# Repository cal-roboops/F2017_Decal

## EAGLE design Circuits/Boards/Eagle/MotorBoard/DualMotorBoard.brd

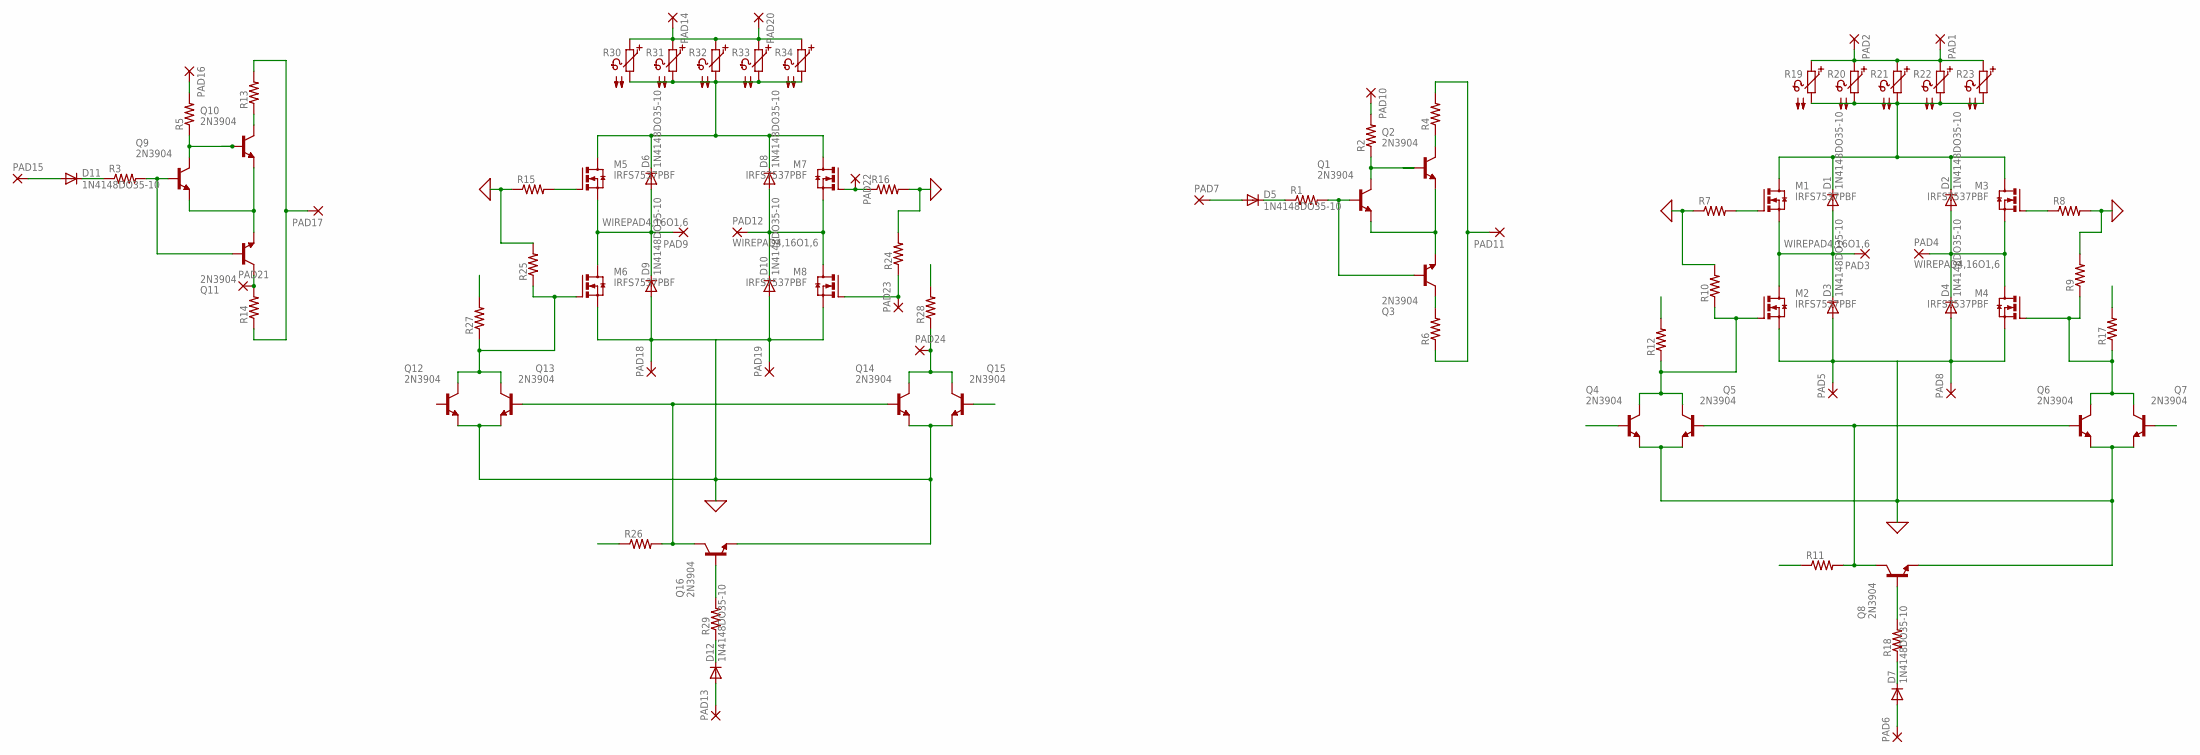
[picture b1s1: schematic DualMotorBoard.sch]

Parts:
D1, D2, D3, D4, D5, D6, D7, D8, D9, D10, D11, D12: 1N4148DO35-10; DO35-10
M1, M2, M3, M4, M5, M6, M7, M8: IRFS7537PBF; D2PACK
PAD1, PAD2, PAD5, PAD8, PAD14, PAD18, PAD19, PAD20: 3,81/1,4
PAD3, PAD4, PAD9, PAD12: WIREPAD4,16O1,6; 4,16O1,6
PAD6, PAD10, PAD11, PAD13, PAD16, PAD17, PAD21, PAD22, PAD23, PAD24: 2,54/1,1
PAD7, PAD15: 2,54/1,0
Q1, Q2, Q3, Q4, Q5, Q6, Q7, Q8, Q9, Q10, Q11, Q12, Q13, Q14, Q15, Q16: 2N3904; TO92
R1, R2, R3, R4, R5, R6, R7, R8, R9, R10, R11, R12, R13, R14, R15, R17, R18, R25, R26, R27, R28, R29: R-US_0207/7; 0207/7
R16, R24: R-US_0207/12; 0207/12
R19, R20, R21, R22, R23, R30, R31, R32, R33, R34: PTC660A; P660A

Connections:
0: D3.A, D4.A, D9.A, D10.A, M2.3 (S), M4.3 (S), M6.3 (S), M8.3 (S), PAD5.1, PAD8.1, PAD18.1, PAD19.1, Q1.3 (E), Q2.3 (E), Q3.3 (E), Q4.3 (E), Q5.3 (E), Q6.3 (E), Q7.3 (E), Q8.3 (E), Q9.3 (E), Q10.3 (E), Q11.3 (E), Q12.3 (E), Q13.3 (E), Q14.3 (E), Q15.3 (E), Q16.3 (E), R7.1, R8.2, R9.2, R10.2, R15.1, R16.2, R24.2, R25.2
BB: Q1.2 (B), Q3.2 (B), Q4.2 (B), R1.2
BB1: Q9.2 (B), Q11.2 (B), R3.2
BF: M3.1 (G), Q3.1 (C), R6.2, R8.1
BFF: PAD21.1, Q11.1 (C), R14.2
BFG: M7.1 (G), PAD22.1, R16.1
DIR: D5.A, PAD7.1
DIR1: D11.A, PAD15.1
FB: Q1.1 (C), Q2.2 (B), Q7.2 (B), R2.1
FB1: Q9.1 (C), Q10.2 (B), Q15.2 (B), R5.1
FF: M1.1 (G), Q2.1 (C), R4.1, R7.2
FF1: M5.1 (G), Q10.1 (C), R13.1, R15.2
MN: D2.A, D4.C, M3.3 (S), M4.2 (D), PAD4.1
MN1: D8.A, D10.C, M7.3 (S), M8.2 (D), PAD12.1
MP: D1.A, D3.C, M1.3 (S), M2.2 (D), PAD3.1
MP1: D6.A, D9.C, M5.3 (S), M6.2 (D), PAD9.1
unnamed: M8.1 (G), PAD23.1, R24.1
unnamed: D7.C, R18.1
unnamed: M6.1 (G), Q12.1 (C), Q13.1 (C), R25.1, R27.1
unnamed: D7.A, PAD6.1
unnamed: PAD24.1, Q14.1 (C), Q15.1 (C), R28.1
unnamed: Q13.2 (B), Q14.2 (B), Q16.1 (C), R26.2
unnamed: Q16.2 (B), R29.2
unnamed: D11.C, R3.1
unnamed: D12.C, R29.1
unnamed: D12.A, PAD13.1
unnamed: Q5.2 (B), Q6.2 (B), Q8.1 (C), R11.2
unnamed: D5.C, R1.1
unnamed: M2.1 (G), Q4.1 (C), Q5.1 (C), R10.1, R12.1
unnamed: Q8.2 (B), R18.2
unnamed: M4.1 (G), Q6.1 (C), Q7.1 (C), R9.1, R17.1
VBAT: PAD1.1, PAD2.1, PAD14.1, PAD20.1, R19.1, R20.1, R21.1, R22.1, R23.1, R30.1, R31.1, R32.1, R33.1, R34.1
VDD: D1.C, D2.C, M1.2 (D), M3.2 (D), R19.2, R20.2, R21.2, R22.2, R23.2
VDD1: D6.C, D8.C, M5.2 (D), M7.2 (D), R30.2, R31.2, R32.2, R33.2, R34.2
VG: PAD11.1, R4.2, R6.1, R12.2, R17.2
VG1: PAD17.1, R13.2, R14.1, R27.2, R28.2
VSW: PAD10.1, R2.2, R11.1
VSW1: PAD16.1, R5.2, R26.1

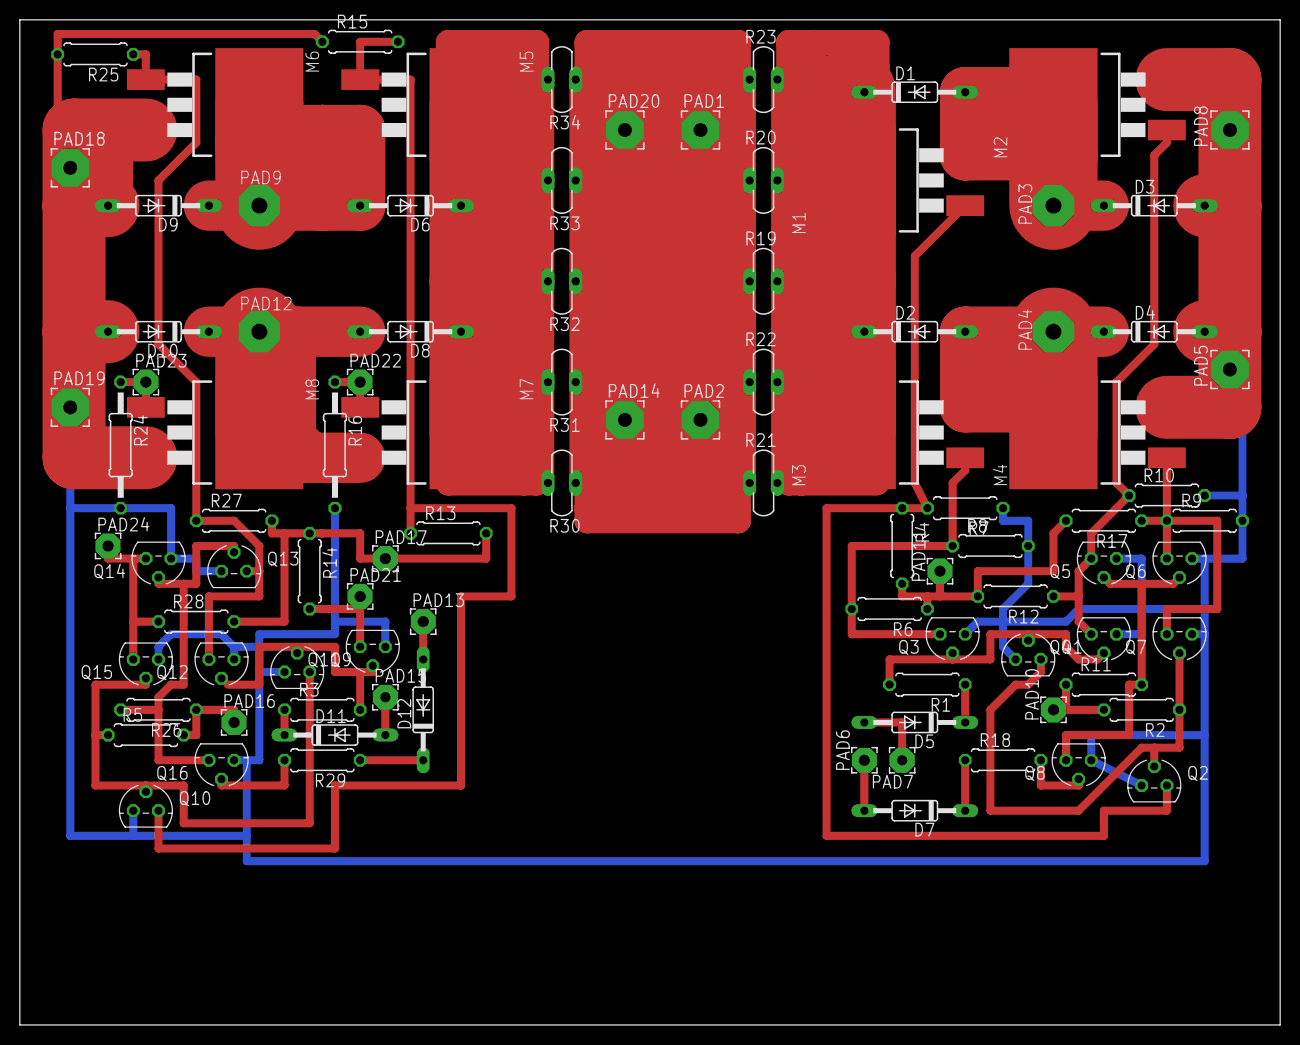
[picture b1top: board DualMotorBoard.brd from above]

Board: 2 copper layers, 127.0 x 101.3 mm, 94 parts (0 on the bottom side), 38 nets.

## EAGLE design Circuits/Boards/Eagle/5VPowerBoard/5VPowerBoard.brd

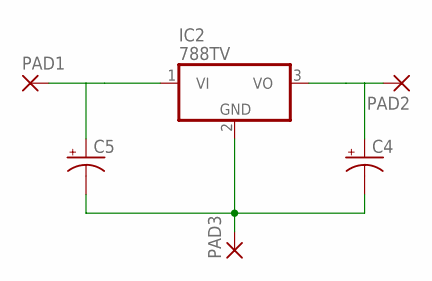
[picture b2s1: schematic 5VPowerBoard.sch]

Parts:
C4, C5: CPOL-USE2.5-7; E2,5-7
IC2: 788TV; TO220V
PAD1, PAD2, PAD3: 3,81/1,4

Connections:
unnamed: C4.-, C5.-, IC2.2 (GND), PAD3.1
VDD: C5.+, IC2.1 (VI), PAD1.1
VSW: C4.+, IC2.3 (VO), PAD2.1

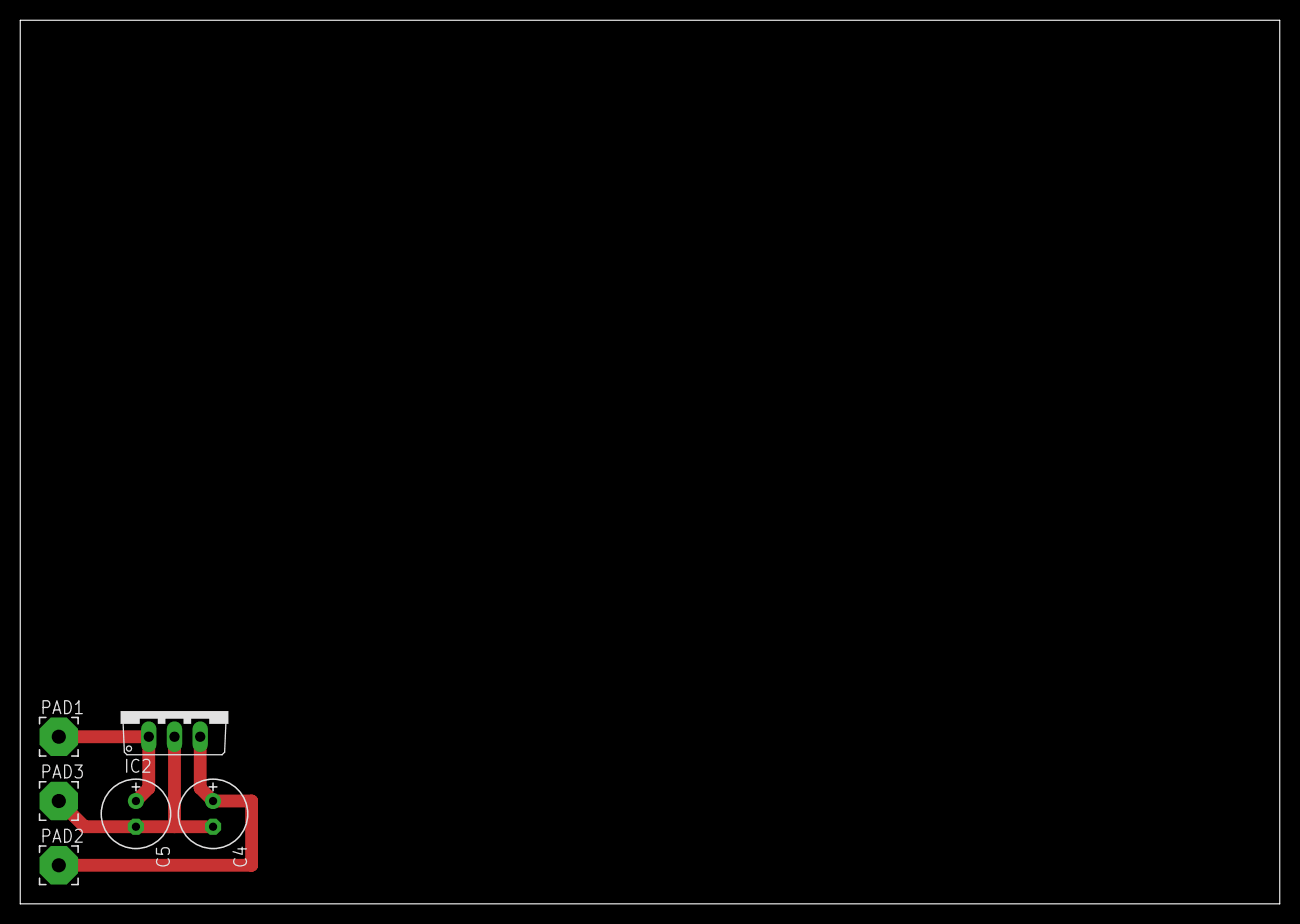
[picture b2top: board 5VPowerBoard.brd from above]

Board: 2 copper layers, 124.4 x 87.3 mm, 6 parts (0 on the bottom side), 3 nets.

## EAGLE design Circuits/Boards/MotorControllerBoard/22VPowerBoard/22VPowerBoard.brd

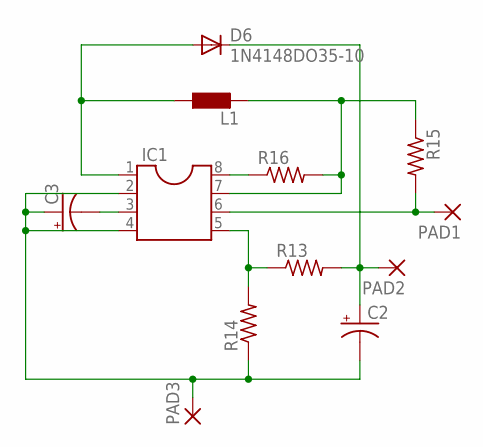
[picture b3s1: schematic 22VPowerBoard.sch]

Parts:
C2, C3: CPOL-USE2.5-7; E2,5-7
D6: 1N4148DO35-10; DO35-10
IC1: DIL8; DIL08
L1: L0207/10; 0207/10
PAD1, PAD2, PAD3: 3,81/1,4
R13, R14, R15, R16: R-US_0207/7; 0207/7

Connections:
unnamed: C2.-, C3.+, IC1.2, IC1.4, PAD3.1, R14.1
unnamed: D6.A, IC1.1, L1.1
unnamed: C3.-, IC1.3
unnamed: IC1.8, R16.1
unnamed: IC1.7, L1.2, R15.1, R16.2
unnamed: IC1.5, R13.1, R14.2
VDD: IC1.6, PAD1.1, R15.2
VG2: C2.+, D6.C, PAD2.1, R13.2

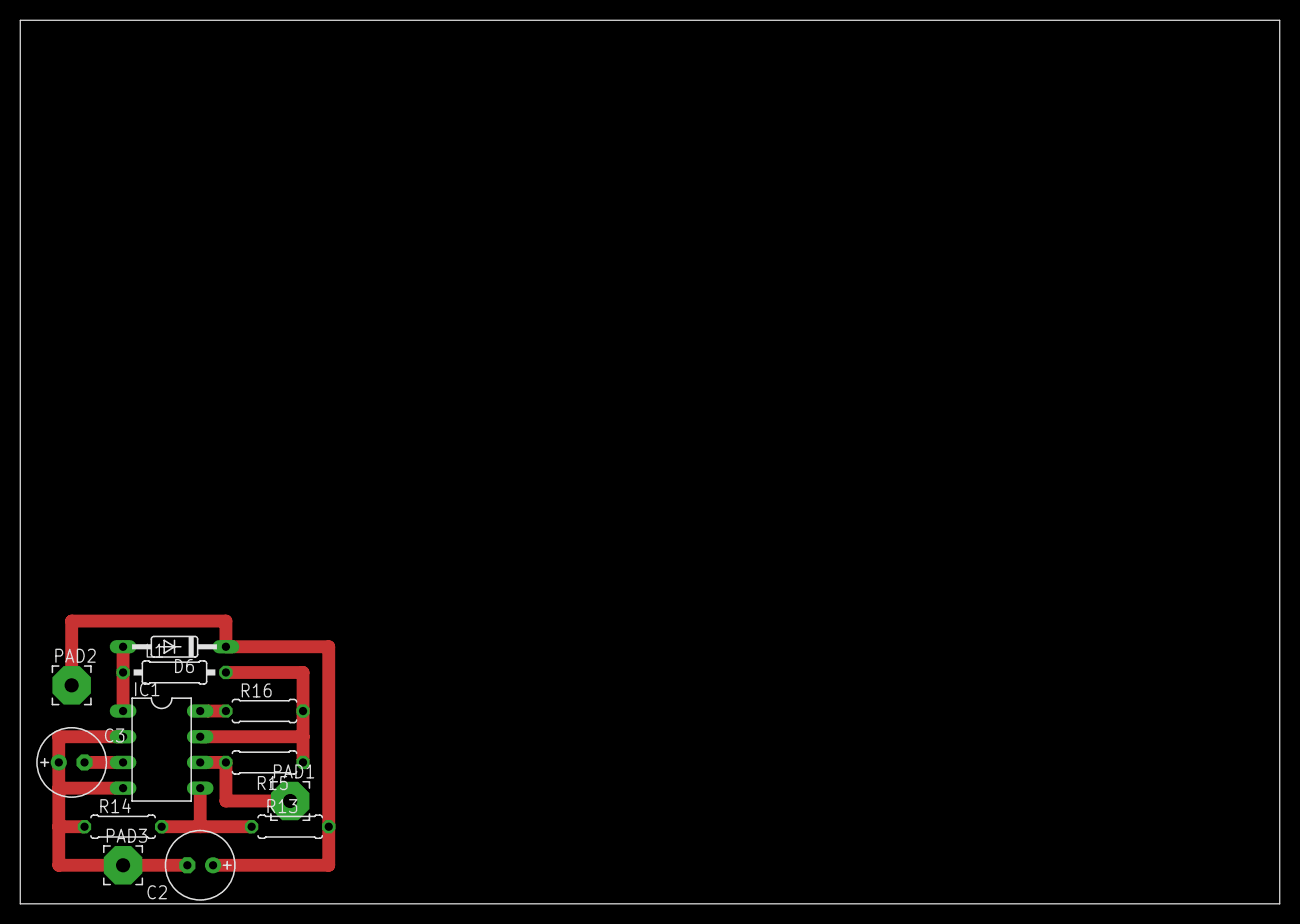
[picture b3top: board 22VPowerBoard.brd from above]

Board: 2 copper layers, 124.4 x 87.3 mm, 12 parts (0 on the bottom side), 8 nets.

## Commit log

2017-08-22 Project creation and gitignore added
2017-08-23 added button that prints to debud
2017-08-23 added text box + submit data button for text box
2017-08-24 made client server with text boxes
2017-08-24 Organization and fine tuning of messenger demo
2017-08-28 local webcam button working
2017-09-18 Added backend server, with basic client, and GUI test client
2017-09-18 Updated gitignore and removed qt exe's
2017-09-21 Added Circuit sims
2017-09-21 Making motor controller feedback loop
2017-09-21 Updated Op-Amp in Logic:
2017-09-25 Updated motor simulation
2017-09-25 Ignore simulation raw files
2017-09-26 Save point before PNP control implementation
2017-09-26 Working motor controller simulation
2017-09-27 Small changes
2017-09-27 Pathing Upload
2017-09-28 Split up motor simulation and defiend high pwoer line
2017-09-30 Updated client/server and made changes to motor controller
2017-10-01 server.cpp V4
2017-10-05 Motor controller updates
2017-10-05 Updated motor controller
2017-10-08 Updated server script and vlc multicast
2017-10-08 Updated proxy client and server classes
2017-10-08 ass1
2017-10-08 Setting up rover client
2017-10-15 deleted Circuits, Pathing, and QtMessengerDemo folders
2017-10-15 Simplified motor controller circuit and added FPGA implmentation specifications
2017-10-16 Updated regulator circuits
2017-10-17 json communication/mutexes/function structs
2017-10-17 server now communicates to rover and back to clients
2017-10-18 updated files
2017-10-18 Added custom motor controller tester
2017-10-25 update all clients
2017-10-25 miscellaneous change
2017-10-25 adding assignment3 code - edward
2017-10-25 git example change
2017-10-25 basic impl of topological pathing done
2017-10-26 cleaned up topological pathing code
2017-10-27 changed path drawing
2017-10-27 made window with buttons that change pages
2017-10-27 added regular controls panel
2017-11-01 Fixed motor controller test code - works as expected now
2017-11-01 tank page
2017-11-01 tank done -- can't move to qtproxy yet
2017-11-03 move control_GUI code to QtProxyClient and two ui windows working
2017-11-03 tank done
2017-11-04 Motor control code updated
2017-11-04 Updated gitigore and removed build-Qt dirs
2017-11-06 Updated encoder reading and motor controller
2017-11-08 updated server/client files; added json.hpp
2017-11-08 removed unnecessary line in server.cpp
2017-11-08 added various python scripts for static image processing
2017-11-08 Removed assignment zip
2017-11-08 fixed buffer reset bug
2017-11-10 bug fix to calc_drops function in pathing
2017-11-10 using variance to calc drops
2017-11-10 finished assignemnt 4 and 5
2017-11-10 finished assignment 4 & 5
    :
    "
2017-11-10 implemented slider label
2017-11-11 Updated SSI for encoder and added programmer
2017-11-11 Cleaned up code in programmer to facilitate bug hunt
2017-11-12 updated client.cpp, server.cpp
2017-11-15 added berkeley map
2017-11-15 fixed typo
2017-11-15 Working on programmer and electronics layout
2017-11-17 added 3 buttons to enable/disable buttons (part 1 of assignment 6)
2017-11-17 implemented new buttons to enable/disable control panel
2017-11-17 implemented buttons
2017-11-17 implememnted control buttons
2017-11-21 updated server.cpp
2017-11-29 fix radio button
2017-11-29 cleaned up pathing script and optimized astar
2017-11-29 control panel with serving working. still need to rename files
2017-11-29 one of the json values was wrong
2017-11-30 fixed access control bug
2017-11-30 fixed key press bug
2017-12-01 fixed some more bugs and styled gui more
2017-12-01 more minor style updates
2017-12-01 first attempt at risk function for a pointcloud
2017-12-01 added comments
2017-12-08 small edit
2017-12-21 Adding PCB motor controller board layout
2017-12-21 Fixed gitignore for eagle files
2017-12-22 Finished board files and updated gitignore
2017-12-22 Fixed board CNC errors, ready for cutting on othermill
2017-12-24 Minor updates to Motor Controller
2017-12-24 Updated 22V circuit for bought parts
2017-12-26 Split off 22V & 5V circuits, shrunk motor controller and began adding second to single board
2017-12-27 Single board, two motor update
2017-12-27 Ported Motor Controller to DesignSpark and generated Gerber files for Othermill
2017-12-28 Started moving from EAGLE to KiCAD
2017-12-30 Update KiCAD motor controller and Version 2 simulation
2017-12-31 Fixed KiCAD motor controller
2018-01-05 Rerouted motor controller for smaller size
2018-01-06 Adjusted PCB design
2018-01-07 Created subcircuit for motor control and routing dual controller
2018-01-07 Finished routing dual motor controller, needs to be cleaned up
2018-01-07 Added 26V and 5V units to the Dual motor controller board
2018-01-07 Fixed missing connections and routing
2018-01-07 Added drain resistors to gates
2018-01-16 Fixed gitignore to allow KiCAD pro files
2018-01-16 Motor HF adjustments (gate drain resistors)
2018-01-16 Finished rerouting board with new resistors and caps
2018-01-16 Updated layout errors
2018-01-17 Motor board circuit updated after prototype cut
2018-01-18 Fixed missing connections and routing errors
2018-01-18 Added pin outputs for battery to ground (for external connections)
2018-01-18 Transferred all JXT connections to bottomw traces
2018-01-24 Added Basic Xilinx Echo program for Arty Z7
2018-01-24 Updated echo to test FPGA functionality in addition to ethernet echo
2018-01-26 Fixed synthesis errors in vivado
2018-01-26 Updated gitignores for Xilinx suite
2018-01-27 Started rover client for FPGA
2018-02-08 setup arm stuff, added a widget for controlling camera mask but it has no functionality yet
2018-02-08 setup example code for how to do the arm in main.cpp
2018-02-08 minor variable names changes
2018-02-14 minor changes
2018-02-14 added release file
2018-02-16 Added NRF24L01+ base files and code
2018-02-17 Moved and updated files
2018-02-20 added some more functionality for drawer
2018-02-24 Added testing for nRF24 module
2018-02-24 FPGA controllers added with base for motor, PI, and servo units
2018-02-24 Updated folder structure, added Quartus library folder, and added SSI test module
2018-02-24 Finished SSI reader testing and added samples/sec functionaility
2018-02-25 QTserver
2018-02-26 server working
2018-02-26 server bugs fixed
2018-02-26 Added ready valid interface, clock generator, and base verilog file for rover arm controller
2018-02-27 Working with Zynq
2018-02-27 Updated async fifo and created async uart interface
2018-02-28 Updating Main rover client
2018-02-28 Updating and moving core GUI files
2018-02-28 Overhall of rover client with new json objects and signal driven architecture
2018-02-28 Updated json functionality
2018-03-01 Updated JSON files and gitignore for QT projects
2018-03-02 updated server
2018-03-06 just deleted unnecessary folder
2018-03-06 added proxy arm functionality but haven't set up JSON transmission - waiting on mitch to specifiy JSON values
2018-03-07 Removed QT build dirs from git
2018-03-07 finished setting up additional functionality - mitch needs to enter in new JSON values and transmit them in new functions
2018-03-08 forgot to add a few things... NOW waiting on mitch to transmit new Json values
2018-03-08 Andy's code switched to Edwards Branch
2018-03-08 commited build for Qt
2018-03-10 Removed FPGA Folder to selectively add non auto generated files
2018-03-10 Selectively added FGPA components back in
2018-03-11 Changed to bare metal C++ application
2018-03-11 Updated FPGA CPP application
2018-03-12 JSON linking and touching up on the GUI. Added cleaner signal slot functionality and send features
2018-03-12 Consistency updates for server with signal slot architecture (currently crashes if rover connection is attempted over and over)
2018-03-13 Finalized GUI updates and connected JSON objects. Updating server to refelect Signal Slot architecture found in GUI.
2018-03-13 Fixed server crashing and added more checks to rover connection thread
2018-03-19 data visualizer demo
2018-03-19 Removed all QtMessengerDemo, main application has been split off from this
2018-03-20 Unified frontend GUI and server to reflect some basic JSON feedback & commands
2018-03-20 Fine tuned server feedback for control options, implemented switch statements for easier code expansion to new cases
2018-03-21 Added more feedback and increased verification of actions in server
2018-03-21 3/21
2018-03-26 Added basic data logging functionality/settings
2018-04-10 setup basic ui and wrote comments on other files
2018-04-12 Debugged SSI waveform off 6600 programmer
2018-04-13 Optimized SSI reader for 6600
2018-04-13 forearm at 90 degrees
2018-04-13 Fixed timeout error for AEAT-6600 progmrammer
2018-04-15 Fixed timing and outputs for both reader and programmer (still fails to program)
2018-04-18 Controllable test arm. Importing into main application and pulluing values still need to be done
2018-04-18 Integrated arm graphic into main gui
2018-04-18 Added qml polling for angle values in scene3D
2018-04-18 Fully integrated arm graphic and updated names to reflect ME parts
2018-11-24 fixed an issue in RoverControlServer/roverthread.cpp
